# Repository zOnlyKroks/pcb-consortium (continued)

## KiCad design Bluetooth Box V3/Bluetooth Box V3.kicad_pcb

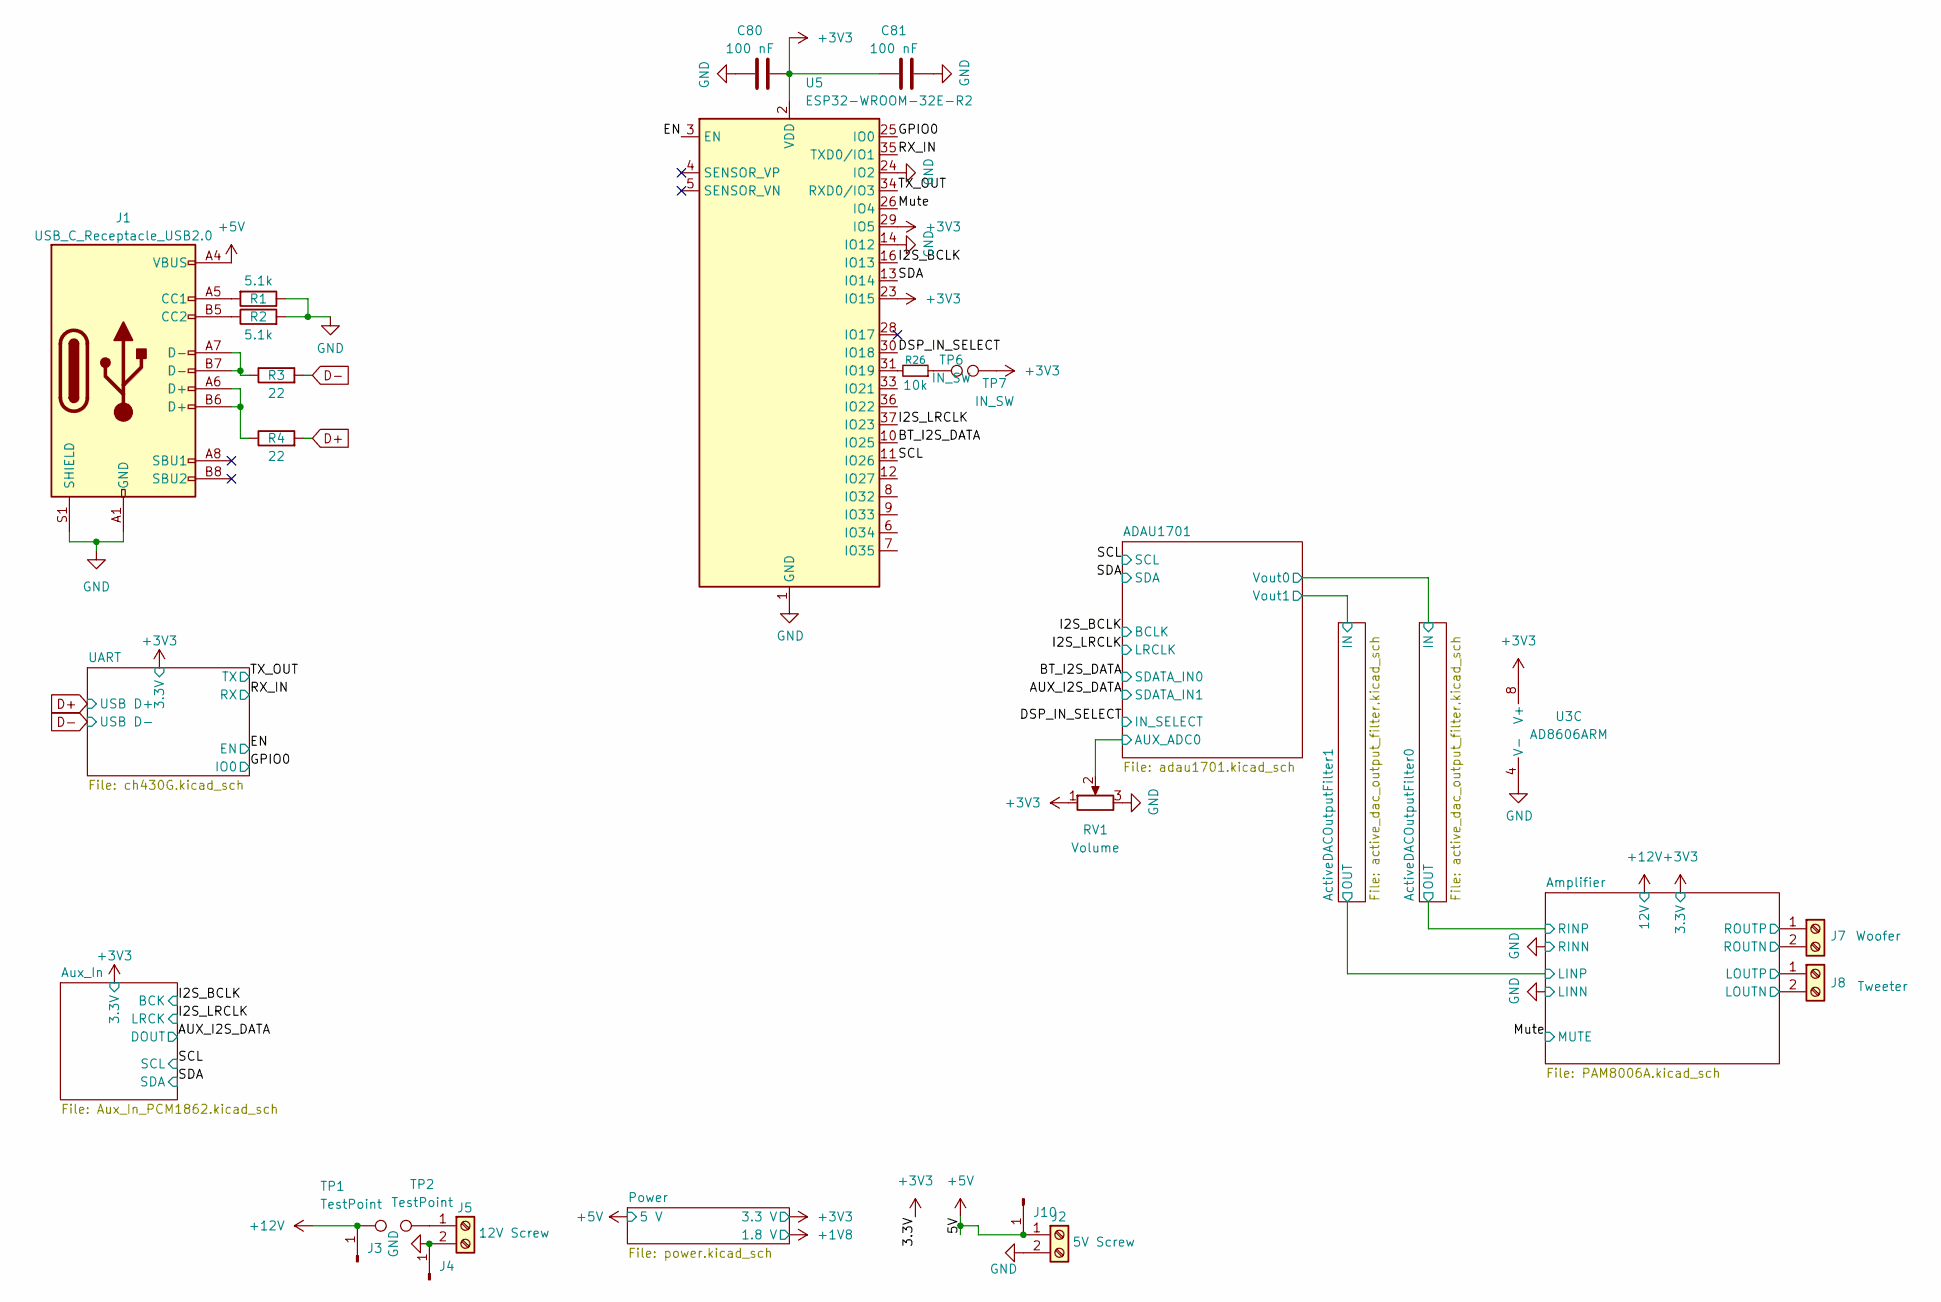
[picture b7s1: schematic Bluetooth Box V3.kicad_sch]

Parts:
C80, C81: 100 nF; C_0805_2012Metric; LCSC Part # C49678
J1: USB_C_Receptacle_USB2.0; USB_C_Receptacle_HRO_TYPE-C-31-M-12; JlcRotOffset 180
J2: 5V Screw; WJ500V-5.08-2P; LCSC Part # C8465
J3, J4, J10: GND; PinHeader_1x01_P2.54mm_Vertical; LCSC Part # C492400
J5: 12V Screw; WJ500V-5.08-2P; LCSC Part # C8465
J7: Woofer; WJ500V-5.08-2P; LCSC Part # C8465
J8: Tweeter; WJ500V-5.08-2P; LCSC Part # C8465
R1, R2: 5.1k; R_0805_2012Metric; LCSC Part # C27834
R3, R4: 22; R_0805_2012Metric; LCSC Part # C17561
R26: 10k; R_0805_2012Metric; LCSC Part # C17414
RV1: Volume; Potentiometer_Bourns_3224J_Horizontal
TP1, TP2: TestPoint; TestPoint_Pad_2.0x2.0mm
TP6, TP7: IN_SW; TestPoint_Pad_2.0x2.0mm
U3: AD8606ARM; MSOP-8_3x3mm_P0.65mm; LCSC Part # C459905
U5: ESP32-WROOM-32E-R2; ESP32-WROOM-32D

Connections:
+3V3: C80.1, C81.2, RV1.1, TP7.1 (1_1), U3.8 (V+), U5.2 (VDD), U5.23 (IO15), U5.29 (IO5); also elsewhere on the board
+5V: J1.A4 (VBUS), J1.A9 (VBUS), J1.B4 (VBUS), J1.B9 (VBUS), J2.1, J10.1 (Pin_1_1); also elsewhere on the board
+12V: J3.1 (Pin_1_1), TP1.1 (1_1); also elsewhere on the board
/ADAU1701/AUX_ADC0: RV1.2; also elsewhere on the board
/Amplifier/LOUTN: J8.2; also elsewhere on the board
/Amplifier/LOUTP: J8.1; also elsewhere on the board
/Amplifier/ROUTN: J7.2; also elsewhere on the board
/Amplifier/ROUTP: J7.1; also elsewhere on the board
/BT_I2S_DATA: U5.10 (IO25); also elsewhere on the board
/DSP_IN_SELECT: U5.30 (IO18); also elsewhere on the board
/EN: U5.3 (EN); also elsewhere on the board
/GPIO0: U5.25 (IO0); also elsewhere on the board
/I2S_BCLK: U5.16 (IO13); also elsewhere on the board
/I2S_LRCLK: U5.37 (IO23); also elsewhere on the board
/Mute: U5.26 (IO4); also elsewhere on the board
/RX_IN: U5.35 (TXD0/IO1); also elsewhere on the board
/SCL: U5.11 (IO26); also elsewhere on the board
/SDA: U5.13 (IO14); also elsewhere on the board
/TX_OUT: U5.34 (RXD0/IO3); also elsewhere on the board
D+: R4.2; also elsewhere on the board
D-: R3.2; also elsewhere on the board
GND: C80.2, C81.1, J1.A1 (GND), J1.A12 (GND), J1.B1 (GND), J1.B12 (GND), J1.S1 (SHIELD), J2.2, J4.1 (Pin_1_1), J5.2, R1.1, R2.2, RV1.3, U3.4 (V-), U5.1 (GND), U5.14 (IO12), U5.15 (GND), U5.24 (IO2), U5.38 (GND), U5.39 (GND); also elsewhere on the board
unnamed: J1.A5 (CC1), R1.2
unnamed: J1.B5 (CC2), R2.1
unnamed: J1.A6 (D+), J1.B6 (D+), R4.1
unnamed: J1.A7 (D-), J1.B7 (D-), R3.1
unnamed: J5.1, TP2.1 (1_1)
unnamed: R26.1, TP6.1 (1_1)
unnamed 73: U3.5 (+); also elsewhere on the board
unnamed 74: U3.6 (-), U3.7; also elsewhere on the board
unnamed: R26.2, U5.31 (IO19)

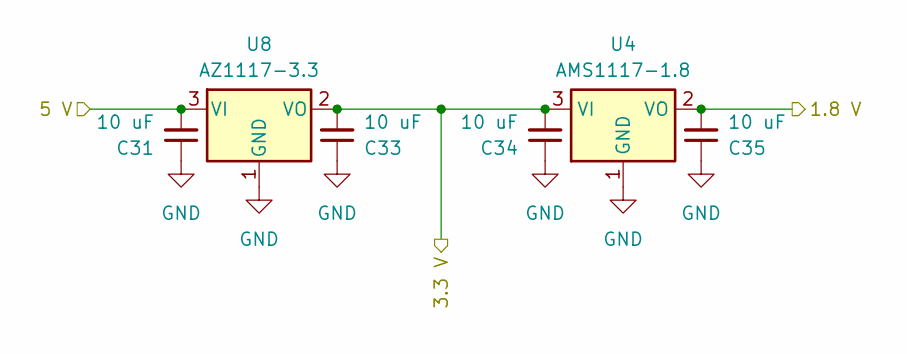
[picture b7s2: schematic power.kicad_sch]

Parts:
C31, C33, C34, C35: 10 uF; C_0805_2012Metric; LCSC Part # C440198
U4: AMS1117-1.8; SOT-223-3_TabPin2; LCSC Part # C46473009
U8: AZ1117-3.3; TO-252-2; LCSC Part # C362112

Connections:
+1V8: C35.2, U4.2 (VO); also elsewhere on the board
+3V3: C33.2, C34.2, U4.3 (VI), U8.2 (VO); also elsewhere on the board
+5V: C31.2, U8.3 (VI); also elsewhere on the board
GND: C31.1, C33.1, C34.1, C35.1, U4.1 (GND), U8.1 (GND); also elsewhere on the board

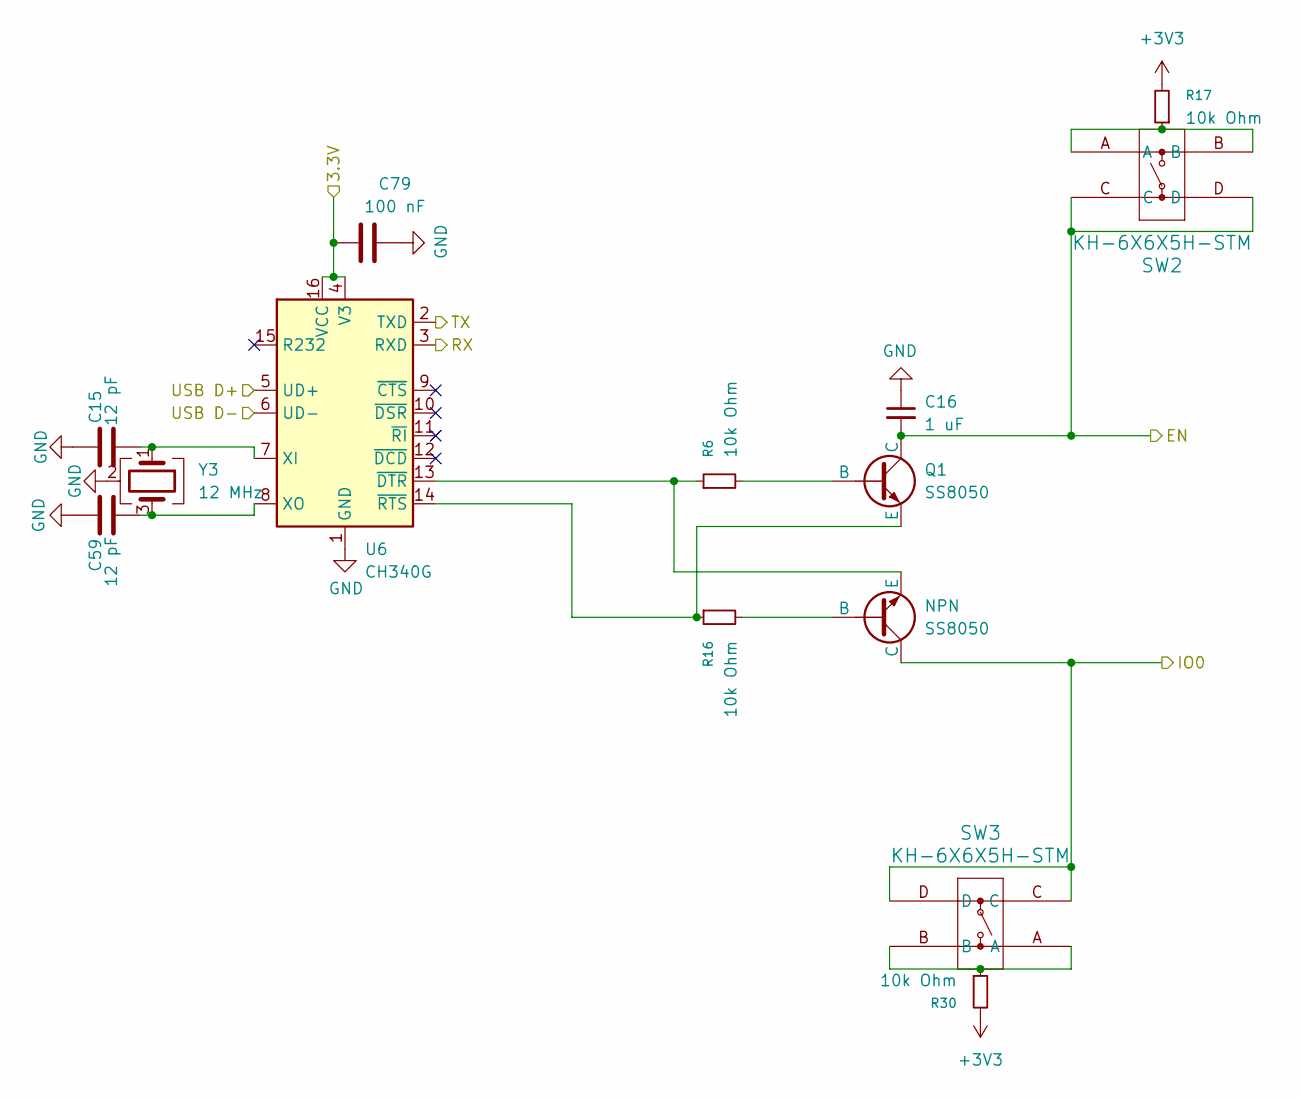
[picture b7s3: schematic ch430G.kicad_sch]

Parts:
C15, C59: 12 pF; C_0805_2012Metric; LCSC Part # C107108
C16: 1 uF; C_0603_1608Metric
C79: 100 nF; C_0805_2012Metric; LCSC Part # C49678
Q1: SS8050; SOT-23
R6, R16, R17, R30: 10k Ohm; R_0805_2012Metric
SS8050: NPN; SOT-23
SW2, SW3: KH-6X6X5H-STM; KH-6X6X5H-STM_SKE
U6: CH340G; SOIC-16_3.9x9.9mm_P1.27mm
Y3: 12 MHz; Crystal_SMD_3225-4Pin_3.2x2.5mm; LCSC Part # C19631429

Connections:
+3V3: C79.2, R17.2, R30.2, U6.4 (V3), U6.16 (VCC); also elsewhere on the board
/EN: C16.2, Q1.1 (C), SW2.C, SW2.D; also elsewhere on the board
/GPIO0: SS8050.1 (C), SW3.C, SW3.D; also elsewhere on the board
/RX_IN: U6.3 (RXD); also elsewhere on the board
/TX_OUT: U6.2 (TXD); also elsewhere on the board
D+: U6.5 (UD+); also elsewhere on the board
D-: U6.6 (UD-); also elsewhere on the board
GND: C15.1, C16.1, C59.1, C79.1, U6.1 (GND), Y3.2 (G), Y3.4 (G); also elsewhere on the board
unnamed: Q1.2 (B), R6.2
unnamed: Q1.3 (E), R16.1, U6.14 (~RTS)
unnamed: R17.1, SW2.A, SW2.B
unnamed: R30.1, SW3.A, SW3.B
unnamed: R16.2, SS8050.2 (B)
unnamed: R6.1, SS8050.3 (E), U6.13 (~DTR)
unnamed: C15.2, U6.7 (XI), Y3.1
unnamed: C59.2, U6.8 (XO), Y3.3

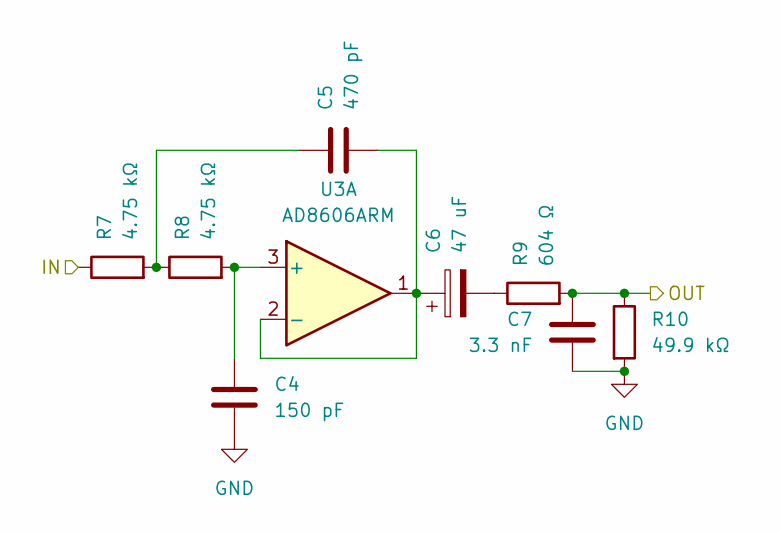
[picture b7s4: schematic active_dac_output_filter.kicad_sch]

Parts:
C4: 150 pF; C_0603_1608Metric_Pad1.08x0.95mm_HandSolder; LCSC Part # C107038
C5: 470 pF; C_0805_2012Metric; LCSC Part # C62771
C6: 47 uF; CP_Elec_6.3x5.4; LCSC Part # C72522
C7: 3.3 nF; C_0805_2012Metric; LCSC Part # C7467177
R7, R8: 4.75 kΩ; R_0805_2012Metric; LCSC Part # C2933451
R9: 604 Ω; R_0805_2012Metric; LCSC Part # C228933
R10: 49.9 kΩ; R_0805_2012Metric; LCSC Part # C469661
U3: AD8606ARM; MSOP-8_3x3mm_P0.65mm; LCSC Part # C459905

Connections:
/ADAU1701/Vout0: R7.1; also elsewhere on the board
/ActiveDACOutputFilter0/OUT: C7.1, R9.2, R10.1; also elsewhere on the board
GND: C4.2, C7.2, R10.2; also elsewhere on the board
unnamed: C5.1, R7.2, R8.1
unnamed: C6.2, R9.1
unnamed: C4.1, R8.2, U3.3 (+)
unnamed: C5.2, C6.1, U3.1, U3.2 (-)
unnamed 73: U3.5 (+); also elsewhere on the board
unnamed 74: U3.6 (-), U3.7; also elsewhere on the board

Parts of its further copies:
C8: 150 pF; C_0603_1608Metric_Pad1.08x0.95mm_HandSolder; LCSC Part # C107038
C9: 470 pF; C_0805_2012Metric; LCSC Part # C62771
C10: 47 uF; CP_Elec_6.3x5.4; LCSC Part # C72522
C11: 3.3 nF; C_0805_2012Metric; LCSC Part # C7467177
R11, R12: 4.75 kΩ; R_0805_2012Metric; LCSC Part # C2933451
R13: 604 Ω; R_0805_2012Metric; LCSC Part # C228933
R14: 49.9 kΩ; R_0805_2012Metric; LCSC Part # C469661

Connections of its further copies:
/ADAU1701/Vout1: R11.1; also elsewhere on the board
/ActiveDACOutputFilter1/OUT: C11.1, R13.2, R14.1; also elsewhere on the board
GND: C8.2, C11.2, R14.2; also elsewhere on the board
unnamed: C9.1, R11.2, R12.1
unnamed: C10.2, R13.1
unnamed 73: C8.1, R12.2; also elsewhere on the board
unnamed 74: C9.2, C10.1; also elsewhere on the board

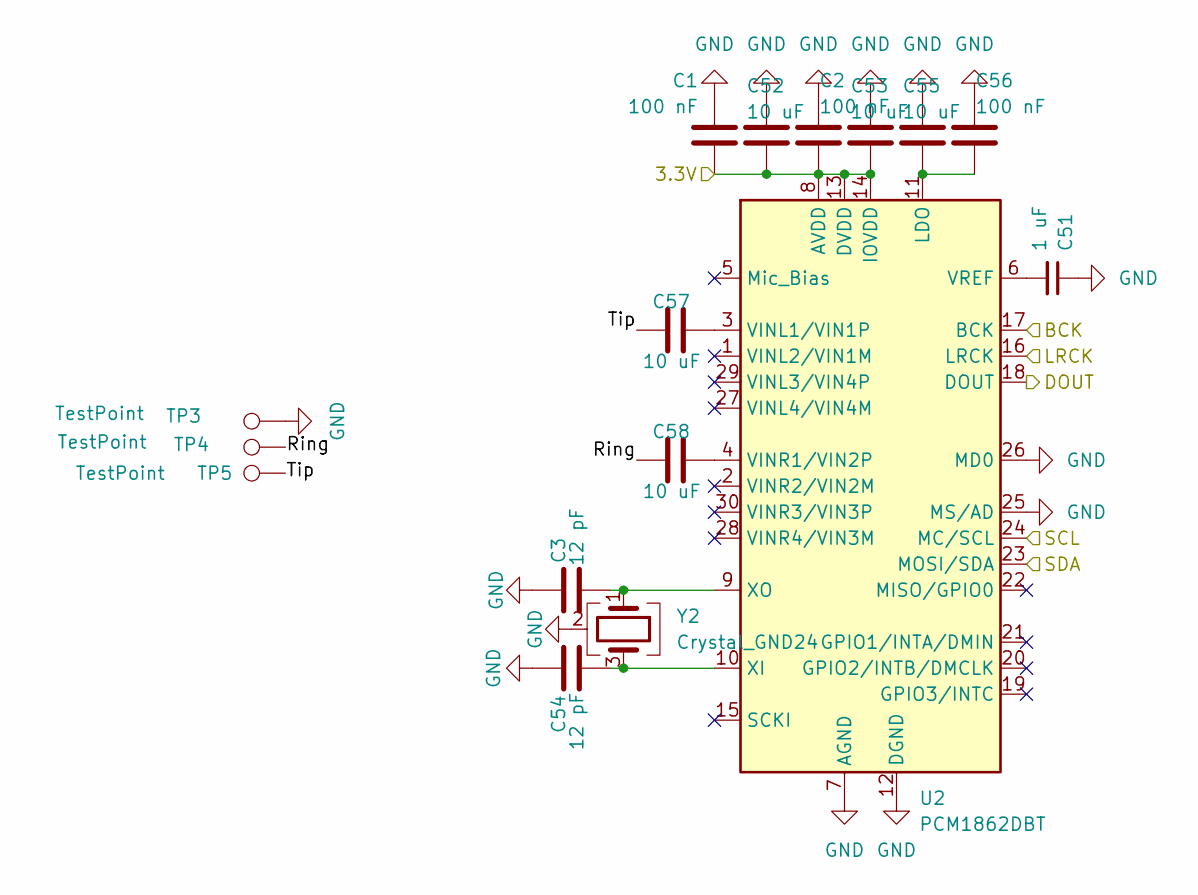
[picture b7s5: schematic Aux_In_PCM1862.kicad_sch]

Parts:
C1, C2, C56: 100 nF; C_0805_2012Metric; LCSC Part # C49678
C3, C54: 12 pF; C_0805_2012Metric; LCSC Part # C107108
C51: 1 uF; C_0805_2012Metric; LCSC Part # C28323
C52, C53, C55, C57, C58: 10 uF; C_0805_2012Metric; LCSC Part # C440198
TP3, TP4, TP5: TestPoint; TestPoint_Pad_2.0x2.0mm
U2: PCM1862DBT; TSSOP-30_4.4x7.8mm_P0.5mm; LCSC Part # C544647
Y2: Crystal_GND24; Crystal_SMD_3225-4Pin_3.2x2.5mm; LCSC Part # C19631429

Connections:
+3V3: C1.2, C2.2, C52.1, C53.1, U2.8 (AVDD), U2.13 (DVDD), U2.14 (IOVDD); also elsewhere on the board
/AUX_I2S_DATA: U2.18 (DOUT); also elsewhere on the board
/Aux_In/Ring: C58.2, TP4.1 (1_1)
/Aux_In/Tip: C57.2, TP5.1 (1_1)
/I2S_BCLK: U2.17 (BCK); also elsewhere on the board
/I2S_LRCLK: U2.16 (LRCK); also elsewhere on the board
/SCL: U2.24 (MC/SCL); also elsewhere on the board
/SDA: U2.23 (MOSI/SDA); also elsewhere on the board
GND: C1.1, C2.1, C3.1, C51.1, C52.2, C53.2, C54.1, C55.2, C56.1, TP3.1 (1_1), U2.7 (AGND), U2.12 (DGND), U2.25 (MS/AD), U2.26 (MD0), Y2.2 (G), Y2.4 (G); also elsewhere on the board
unnamed: C55.1, C56.2, U2.11 (LDO)
unnamed: C57.1, U2.3 (VINL1/VIN1P)
unnamed: C58.1, U2.4 (VINR1/VIN2P)
unnamed: C51.2, U2.6 (VREF)
unnamed: C54.2, U2.10 (XI), Y2.3
unnamed: C3.2, U2.9 (XO), Y2.1

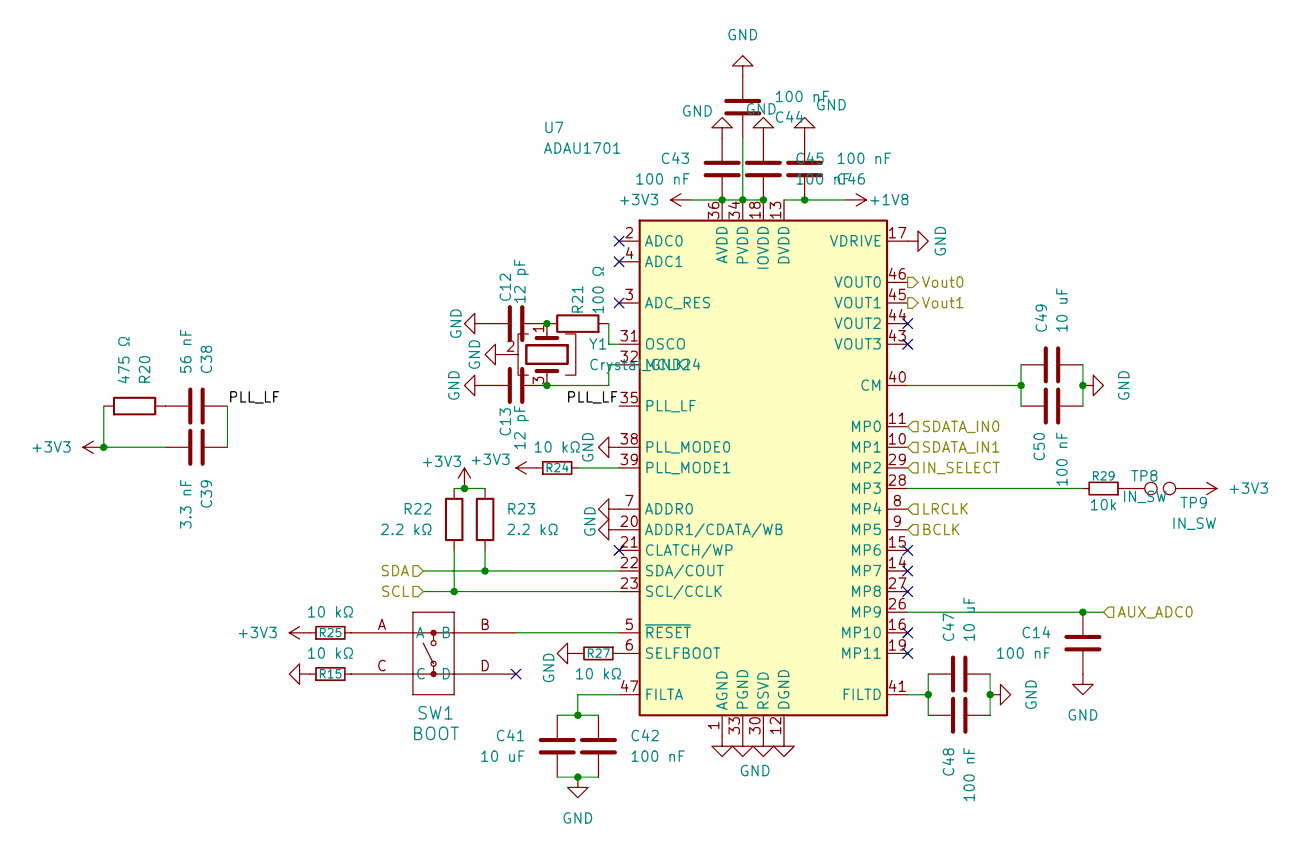
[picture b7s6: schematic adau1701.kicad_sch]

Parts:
C12, C13: 12 pF; C_0805_2012Metric; LCSC Part # C107108
C14, C42, C43, C44, C45, C46, C48, C50: 100 nF; C_0805_2012Metric; LCSC Part # C49678
C38: 56 nF; C_0805_2012Metric; LCSC Part # C107156
C39: 3.3 nF; C_0805_2012Metric; LCSC Part # C7467177
C41, C47, C49: 10 uF; C_0805_2012Metric; LCSC Part # C440198
R15, R24, R25, R27: 10 kΩ; R_0805_2012Metric; LCSC Part # C84376
R20: 475 Ω; R_0805_2012Metric; LCSC Part # C204528
R21: 100 Ω; R_0805_2012Metric; LCSC Part # C17408
R22, R23: 2.2 kΩ; R_0805_2012Metric; LCSC Part # C17520
R29: 10k; R_0805_2012Metric; LCSC Part # C17414
SW1: BOOT; KH-6X6X5H-STM_SKE; LCSC Part # C2837531
TP8, TP9: IN_SW; TestPoint_Pad_2.0x2.0mm
U7: ADAU1701; LQFP-48_7x7mm_P0.5mm; LCSC Part # C389590
Y1: Crystal_GND24; Crystal_SMD_3225-4Pin_3.2x2.5mm; LCSC Part # C19631429

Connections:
+1V8: C46.1, U7.13 (DVDD), U7.24 (DVDD); also elsewhere on the board
+3V3: C39.2, C43.2, C44.1, C45.2, R20.2, R22.1, R23.1, R24.1, R25.1, TP9.1 (1_1), U7.18 (IOVDD), U7.34 (PVDD), U7.36 (AVDD), U7.48 (AVDD); also elsewhere on the board
/ADAU1701/AUX_ADC0: C14.2, U7.26 (MP9); also elsewhere on the board
/ADAU1701/PLL_LF: C38.1, C39.1, U7.35 (PLL_LF)
/ADAU1701/Vout0: U7.46 (VOUT0); also elsewhere on the board
/ADAU1701/Vout1: U7.45 (VOUT1); also elsewhere on the board
/AUX_I2S_DATA: U7.10 (MP1); also elsewhere on the board
/BT_I2S_DATA: U7.11 (MP0); also elsewhere on the board
/DSP_IN_SELECT: U7.29 (MP2); also elsewhere on the board
/I2S_BCLK: U7.9 (MP5); also elsewhere on the board
/I2S_LRCLK: U7.8 (MP4); also elsewhere on the board
/SCL: R22.2, U7.23 (SCL/CCLK); also elsewhere on the board
/SDA: R23.2, U7.22 (SDA/COUT); also elsewhere on the board
GND: C12.1, C13.1, C14.1, C41.1, C42.2, C43.1, C44.2, C45.1, C46.2, C47.2, C48.2, C49.2, C50.2, R15.1, R27.2, U7.1 (AGND), U7.7 (ADDR0), U7.12 (DGND), U7.17 (VDRIVE), U7.20 (ADDR1/CDATA/WB), U7.25 (DGND), U7.30 (RSVD), U7.33 (PGND), U7.37 (AGND), U7.38 (PLL_MODE0), U7.42 (AGND), Y1.2 (G), Y1.4 (G); also elsewhere on the board
unnamed: C12.2, R21.1, Y1.1
unnamed: C38.2, R20.1
unnamed: R15.2, SW1.C
unnamed: R25.2, SW1.A
unnamed: R29.1, TP8.1 (1_1)
unnamed: C49.1, C50.1, U7.40 (CM)
unnamed: C41.2, C42.1, U7.47 (FILTA)
unnamed: C47.1, C48.1, U7.41 (FILTD)
unnamed: C13.2, U7.32 (MCLKI), Y1.3
unnamed: R29.2, U7.28 (MP3)
unnamed: R21.2, U7.31 (OSCO)
unnamed: R24.2, U7.39 (PLL_MODE1)
unnamed: R27.1, U7.6 (SELFBOOT)
unnamed: SW1.B, U7.5 (~RESET)

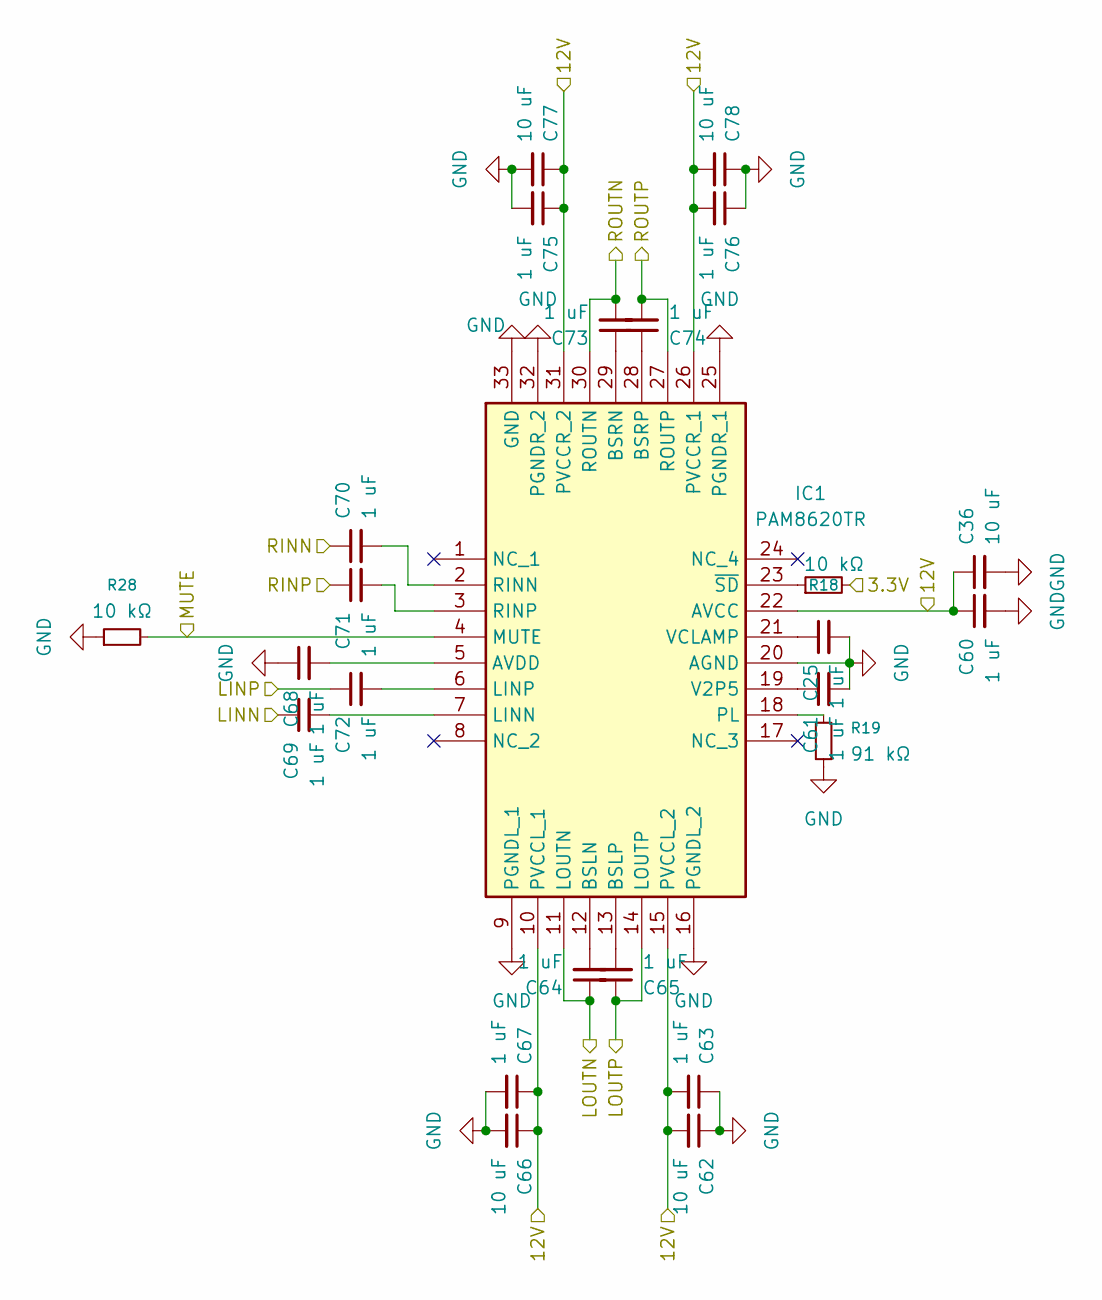
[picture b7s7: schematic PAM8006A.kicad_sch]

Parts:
C25, C60, C61, C63, C64, C65, C67, C68, C69, C70, C71, C72, C73, C74, C75, C76: 1 uF; C_0805_2012Metric; LCSC Part # C28323
C36, C62, C66, C77, C78: 10 uF; C_0805_2012Metric; LCSC Part # C440198
IC1: PAM8620TR; Mouser Part Number 621-PAM8620TR
R18, R28: 10 kΩ; R_0805_2012Metric; LCSC Part # C84376
R19: 91 kΩ; R_0805_2012Metric; LCSC Part # C2933509

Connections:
+3V3: R18.2; also elsewhere on the board
+12V: C36.1, C60.1, C62.2, C63.2, C66.1, C67.1, C75.1, C76.2, C77.1, C78.2, IC1.10 (PVCCL_1), IC1.15 (PVCCL_2), IC1.22 (AVCC), IC1.26 (PVCCR_1), IC1.31 (PVCCR_2); also elsewhere on the board
/ActiveDACOutputFilter0/OUT: C71.1; also elsewhere on the board
/ActiveDACOutputFilter1/OUT: C72.1; also elsewhere on the board
/Amplifier/LOUTN: C64.1, IC1.11 (LOUTN); also elsewhere on the board
/Amplifier/LOUTP: C65.1, IC1.14 (LOUTP); also elsewhere on the board
/Amplifier/ROUTN: C73.2, IC1.30 (ROUTN); also elsewhere on the board
/Amplifier/ROUTP: C74.2, IC1.27 (ROUTP); also elsewhere on the board
/Mute: IC1.4 (MUTE), R28.2; also elsewhere on the board
GND: C25.2, C36.2, C60.2, C61.2, C62.1, C63.1, C66.2, C67.2, C68.1, C69.1, C70.1, C75.2, C76.1, C77.2, C78.1, IC1.9 (PGNDL_1), IC1.16 (PGNDL_2), IC1.20 (AGND), IC1.25 (PGNDR_1), IC1.32 (PGNDR_2), IC1.33 (GND), R19.1, R28.1; also elsewhere on the board
unnamed: C68.2, IC1.5 (AVDD)
unnamed: C64.2, IC1.12 (BSLN)
unnamed: C65.2, IC1.13 (BSLP)
unnamed: C73.1, IC1.29 (BSRN)
unnamed: C74.1, IC1.28 (BSRP)
unnamed: C69.2, IC1.7 (LINN)
unnamed: C72.2, IC1.6 (LINP)
unnamed: IC1.18 (PL), R19.2
unnamed: C70.2, IC1.2 (RINN)
unnamed: C71.2, IC1.3 (RINP)
unnamed: C61.1, IC1.19 (V2P5)
unnamed: C25.1, IC1.21 (VCLAMP)
unnamed: IC1.23 (~SD), R18.1

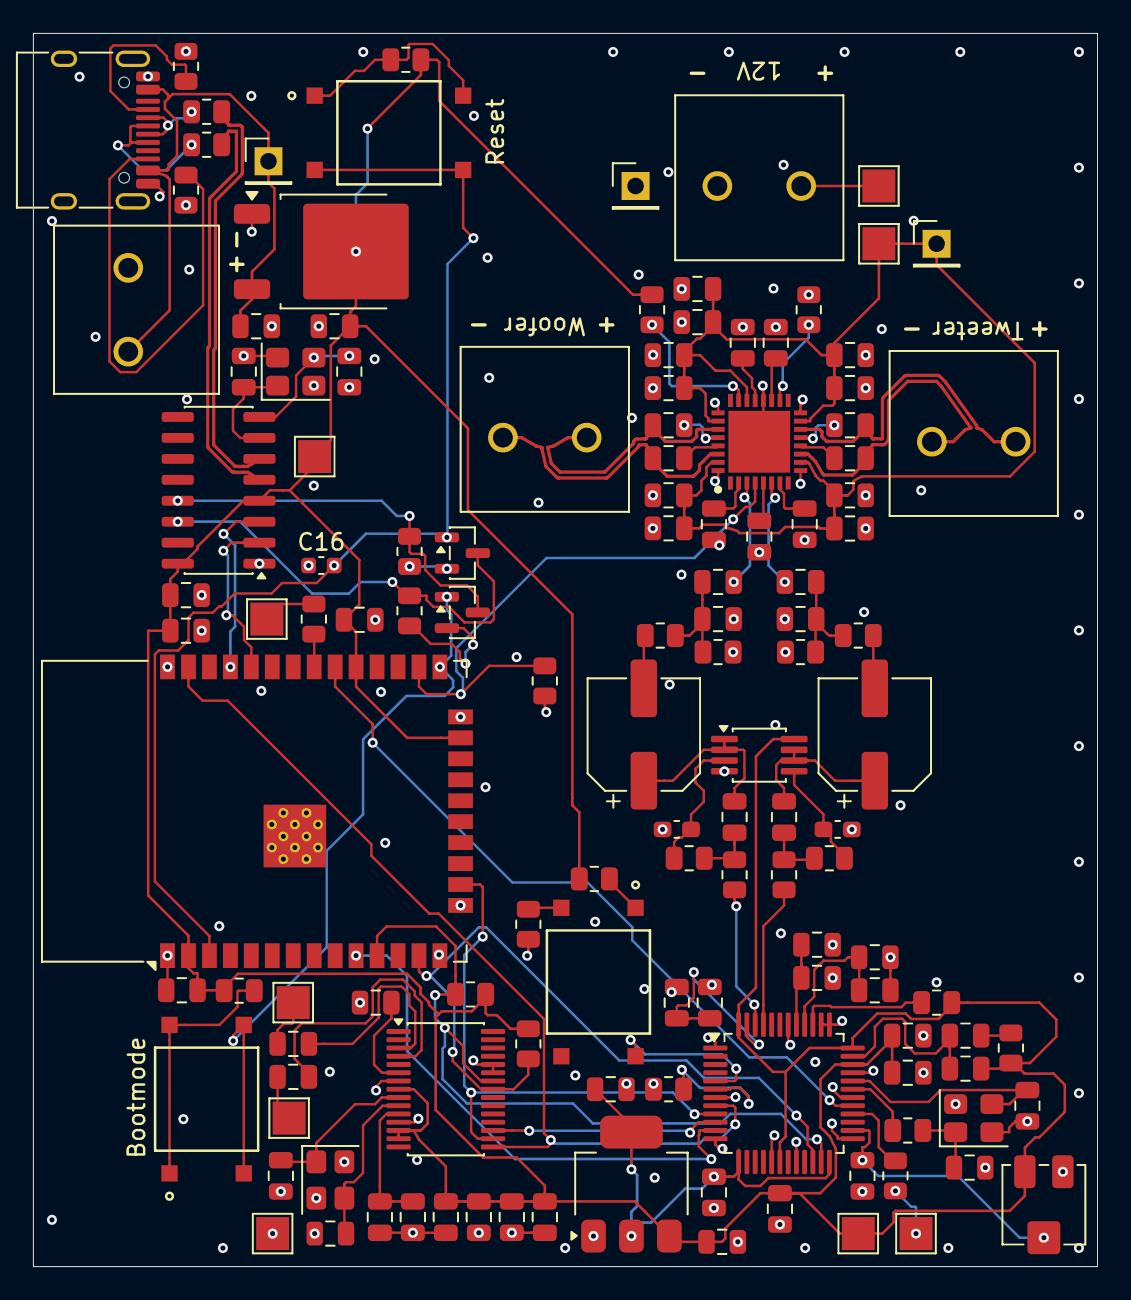
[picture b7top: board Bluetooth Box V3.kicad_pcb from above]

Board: 4 copper layers, 64.5 x 74.8 mm, 129 parts (0 on the bottom side), 87 nets.

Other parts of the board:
C82: 100 nF; C_0805_2012Metric

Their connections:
+3V3: C82.1; also elsewhere on the board
GND: C82.2; also elsewhere on the board

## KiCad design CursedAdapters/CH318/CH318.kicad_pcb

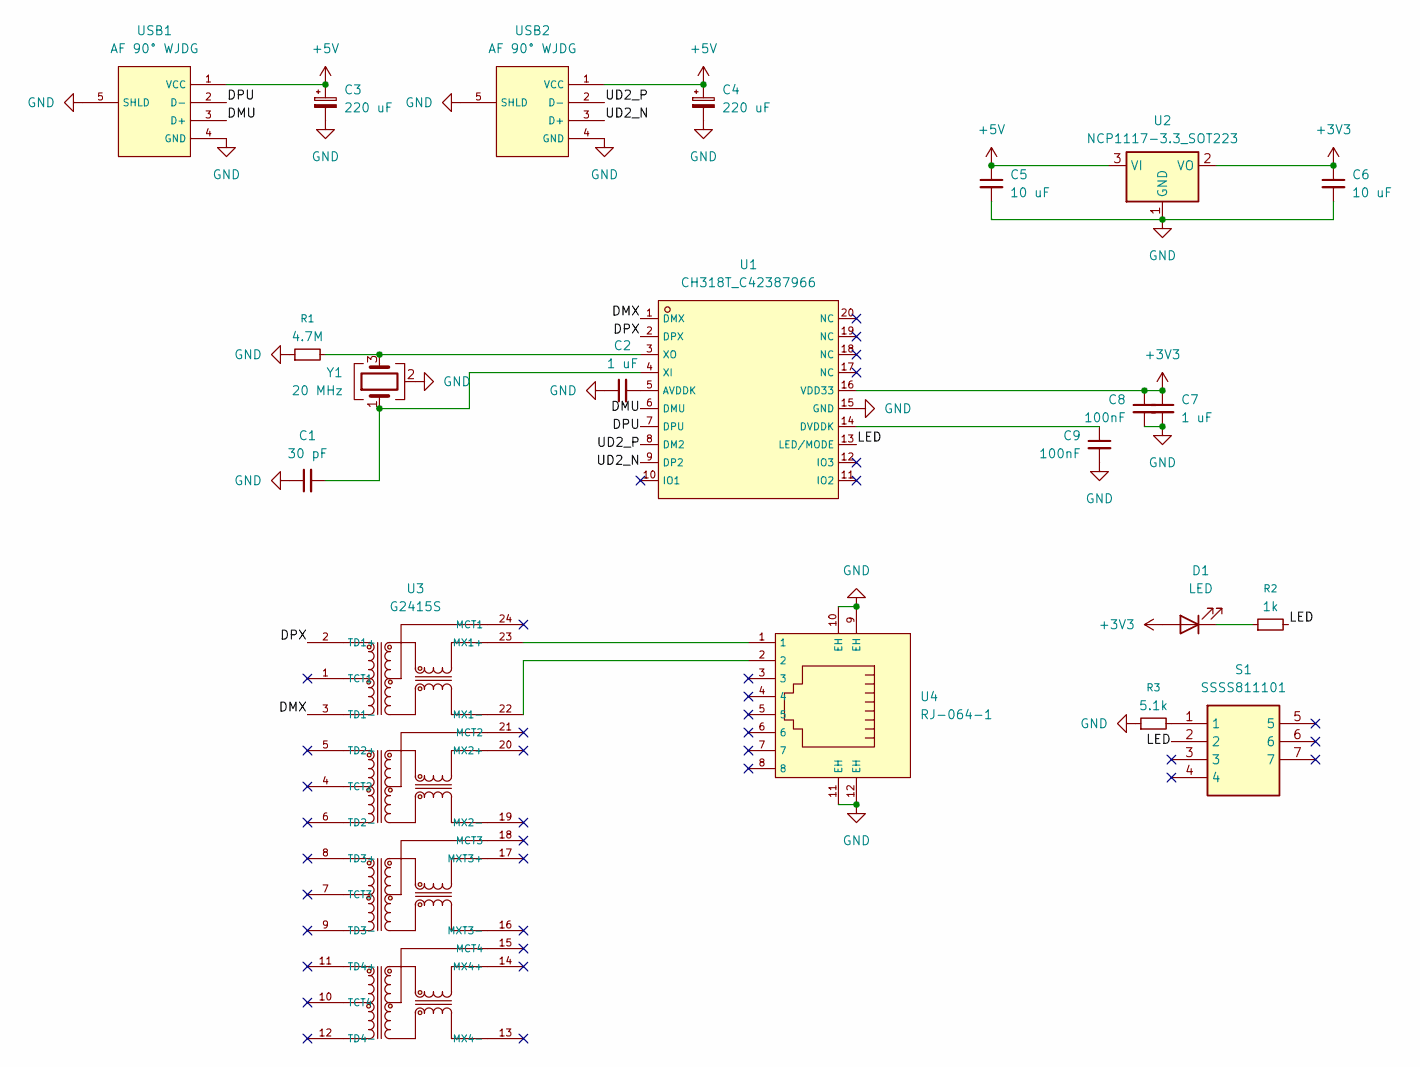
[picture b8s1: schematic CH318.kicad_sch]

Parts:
C1: 30 pF; C_0603_1608Metric
C2, C7: 1 uF; C_0805_2012Metric
C3, C4: 220 uF
C5, C6: 10 uF; C_0805_2012Metric
C8, C9: 100nF; C_0603_1608Metric
D1: LED; LED_0805_2012Metric
R1: 4.7M; R_0603_1608Metric
R2: 1k; R_0603_1608Metric
R3: 5.1k; R_0603_1608Metric
S1: SSSS811101; Mouser Part Number 688-SSSS811101
U1: CH318T_C42387966; C42387966_TSSOP-20_L6_5-W4_4-P0_65-LS6_4-BL; LCSC C42387966
U2: NCP1117-3.3_SOT223; SOT-223-3_TabPin2
U3: G2415S; C3003219_SMD-24_L15_1-W7_1-P1_00-LS10_0-BL; LCSC C3003219
U4: RJ-064-1; C7205199_CONN-SMD_RJ-064; LCSC C7205199
USB1, USB2: AF 90° WJDG; C456018_USB-A-TH_AF-WJDG; LCSC C456018
Y1: 20 MHz; Crystal_SMD_3225-4Pin_3.2x2.5mm

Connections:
+3V3: C6.1, C7.1, C8.1, D1.2 (A), U1.16 (VDD33), U2.2 (VO)
+5V: C3.1, C4.1, C5.1, U2.3 (VI), USB1.1 (VCC), USB2.1 (VCC)
/DMU: U1.6 (DMU), USB1.3 (D+)
/DMX: U1.1 (DMX), U3.3 (TD1-)
/DPU: U1.7 (DPU), USB1.2 (D-)
/DPX: U1.2 (DPX), U3.2 (TD1+)
/LED: R2.2, S1.2, U1.13 (LED/MODE)
/UD2_N: U1.9 (DP2), USB2.3 (D+)
/UD2_P: U1.8 (DM2), USB2.2 (D-)
GND: C1.1, C2.1, C3.2, C4.2, C5.2, C6.2, C7.2, C8.2, C9.2, R1.1, R3.1, U1.15 (GND), U2.1 (GND), U4.9 (EH), U4.10 (EH), U4.11 (EH), U4.12 (EH), USB1.4 (GND), USB1.5 (SHLD), USB2.4 (GND), USB2.5 (SHLD), Y1.2 (G), Y1.4 (G)
unnamed: D1.1 (K), R2.1
unnamed: R3.2, S1.1
unnamed: C2.2, U1.5 (AVDDK)
unnamed: C9.1, U1.14 (DVDDK)
unnamed: C1.2, U1.4 (XI), Y1.1
unnamed: R1.2, U1.3 (XO), Y1.3
unnamed: U3.23 (MX1+), U4.1
unnamed: U3.22 (MX1-), U4.2

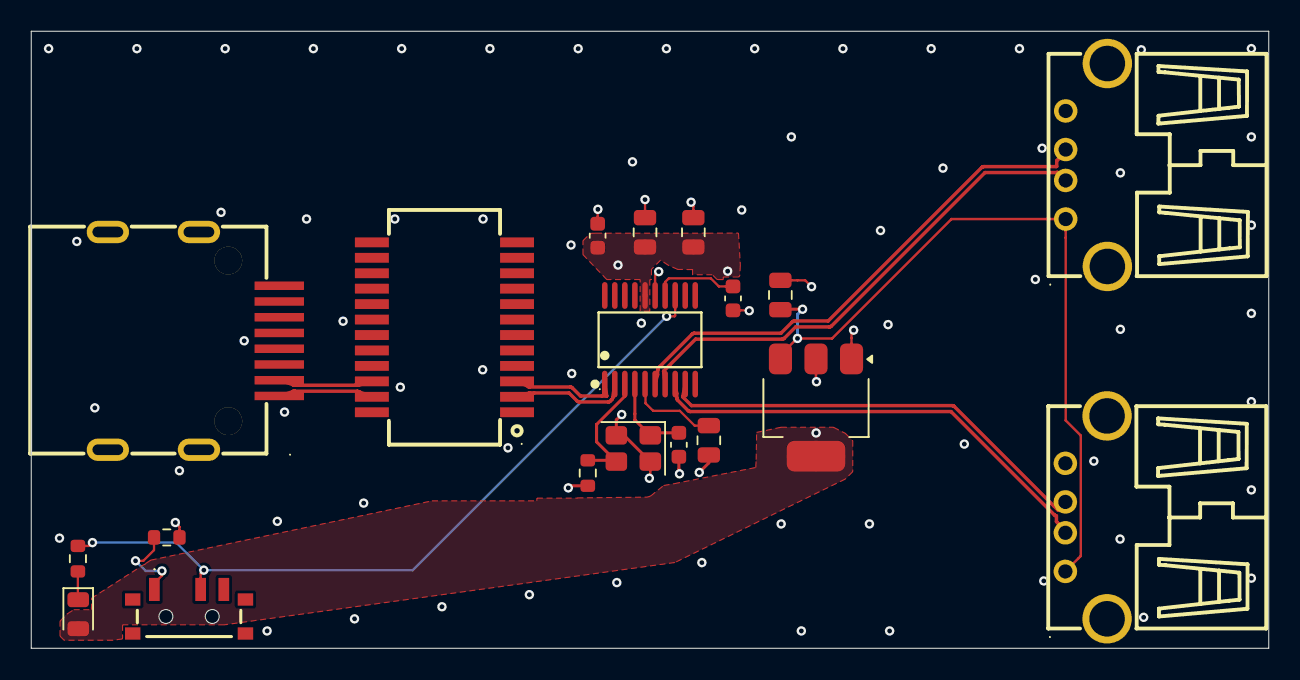
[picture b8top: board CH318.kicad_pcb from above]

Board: 4 copper layers, 80.1 x 40.0 mm, 19 parts (0 on the bottom side), 18 nets.
